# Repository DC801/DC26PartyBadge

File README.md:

# DC801 DC26 Party Badge
Party badge and BLE hardware board

# Hardware
 - **Rigado BMD-300** Bluetooth low energy based on a Nordic nRF52832
   - 16MHz ARM® Cortex™ M4F CPU, 512kB of flash memory, 64kB RAM
   - [https://www.rigado.com/product/bmd-300/](https://www.rigado.com/product/bmd-300/)
 ***
 - **Lots of I/O**
   - Speaker
   - 6 buttons
   - One hidden button
   - SPI LCD screen
   - Selected pin breakouts
   - JTAG interface
   - Micro USB
   - microSD card
   - 2 SAO connectors
   - 2 minibadges
 ***
 - A MCP73831 LiPo battery charger
 - Kickass silkscreen

Board design is in Kicad

See the [Hardware](/Hardware) directory for more info, schematics and etc

# SD Card

Format your SD card as FAT32 and copy the contents of [SD_Card](SD_Card) into it

# Software
 - Environment is GNU ARM GCC with your choice of IDE (I used CLion)
 - Need a J-Link Segger JTAG programmer
 - Uses the softdevice s132

See the [Software](/Software) directory for more info

# What's it do?

Awesome **things**, that's what!  See the [Software](Software) directory for more information.

# More info

Follow [@rushan_ee](http://twitter.com/rushan_ee) or [@hamster](http://twitter.com/hamster) for updates

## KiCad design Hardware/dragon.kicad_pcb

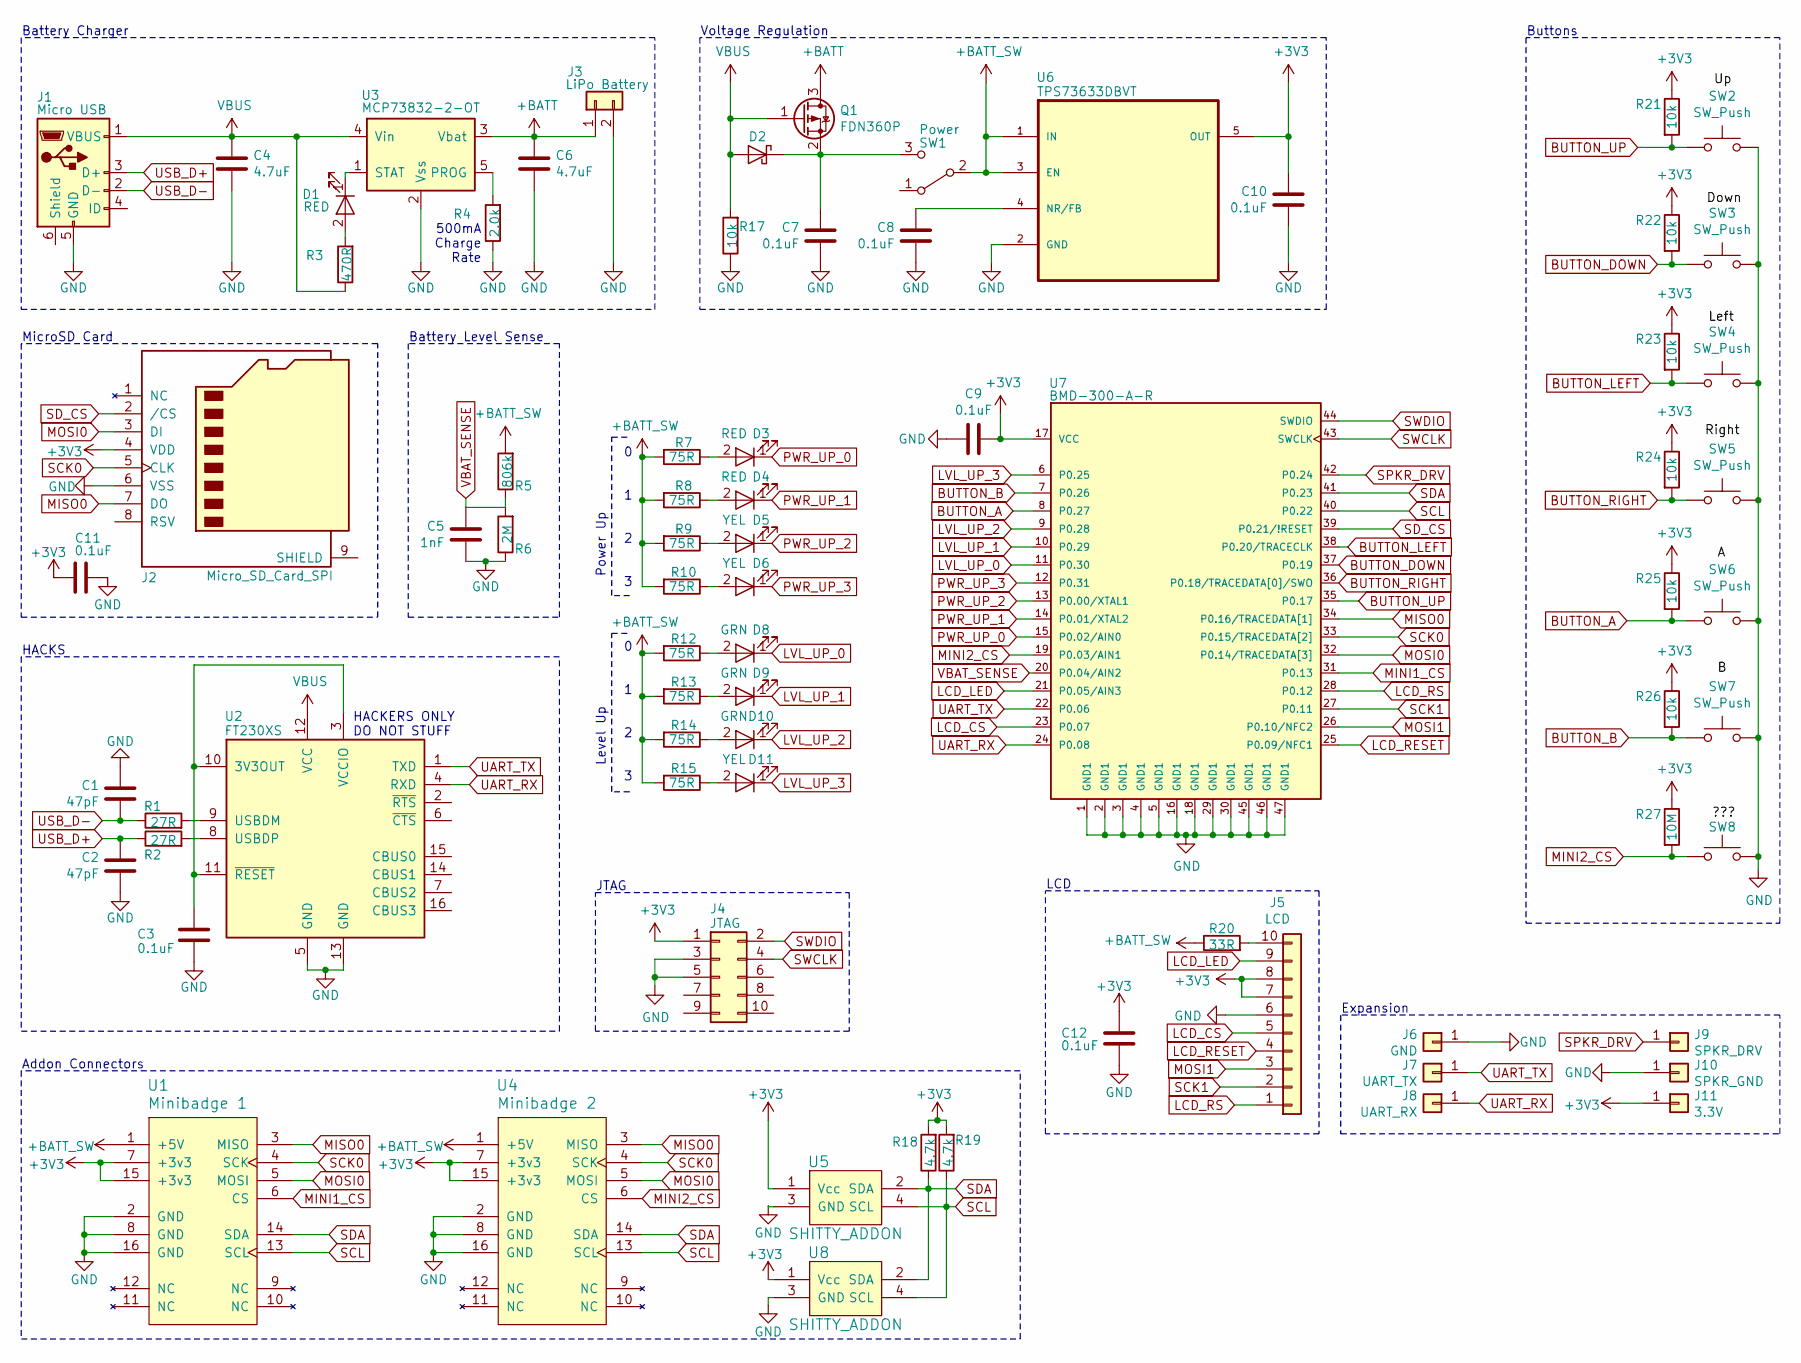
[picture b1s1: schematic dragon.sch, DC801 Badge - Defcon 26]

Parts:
C1, C2: 47pF; C_0201
C3, C7, C8, C9, C10, C11, C12: 0.1uF; C_0201
C4, C6: 4.7uF; C_0603
C5: 1nF; C_0201
D1, D3, D4: RED; LED_0603
D2: D_Schottky; D_0603
D5, D6, D11: YEL; LED_0603
D8, D9, D10: GRN; LED_0603
J1: Micro USB; MicroUSB-10118192-0001LF
J2: Micro_SD_Card_SPI; MicroSD-Socket-1140084168
J3: LiPo Battery; JST_PH_S2B-PH-SM4-TB_02x2.00mm_Angled
J4: JTAG; Pin_Header_Straight_2x05_Pitch1.27mm_SMD
J5: LCD; XF2L-1035-1A
J6: GND; SolderWirePad_single_0-8mmDrill
J7: UART_TX; SolderWirePad_single_0-8mmDrill
J8: UART_RX; SolderWirePad_single_0-8mmDrill
J9: SPKR_DRV; SolderWirePad_single_0-8mmDrill
J10: SPKR_GND; SolderWirePad_single_0-8mmDrill
J11: 3.3V; SolderWirePad_single_0-8mmDrill
Q1: FDN360P; SuperSOT-3
R1, R2: 27R; R_0201
R3: 470R; R_0201
R4: 2.0k; R_0201
R5: 806k; R_0201
R6: 2M; R_0201
R7, R8, R9, R10, R12, R13, R14, R15: 75R; R_0201
R17, R21, R22, R23, R24, R25, R26: 10k; R_0201
R18, R19: 4.7k; R_0201
R20: 33R; R_0201
R27: 10M; R_0201
SW1: Power; SW_SPDT_CK-JS102011SAQN
SW2, SW3, SW4, SW5, SW6, SW7: SW_Push; SW_SPST_B3S-1000
SW8: TEST_2P; Test_Point_2Pads
U1: Minibadge 1; SAINTCON-Minibadge
U2: FT230XS; SSOP-16_3.9x4.9mm_Pitch0.635mm
U3: MCP73832-2-OT; TSOT-23-5
U4: Minibadge 2; SAINTCON-Minibadge
U5, U8: SHITTY_ADDON; Badgelife-Shitty-2x2-NotRotated
U6: TPS73633DBVT; TSOT-23-5
U7: BMD-300-A-R; RIGADO_BMD-300-A-R

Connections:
+3V3: C9.1, C10.1, C11.2, C12.2, J2.4 (VDD), J4.1, J5.7, J5.8, J11.1, R18.2, R19.2, R21.1, R22.1, R23.1, R24.1, R25.1, R26.1, R27.1, U1.7 (+3v3), U1.15 (+3v3), U4.7 (+3v3), U4.15 (+3v3), U5.1 (Vcc), U6.5 (OUT), U7.17 (VCC), U8.1 (Vcc)
+BATT: C6.2, J3.1, Q1.3 (D), U3.3 (Vbat)
+BATT_SW: R5.2, R7.2, R8.2, R9.2, R10.2, R12.2, R13.2, R14.2, R15.2, R20.1, SW1.2 (B), U1.1 (+5V), U4.1 (+5V), U6.1 (IN), U6.3 (EN)
BUTTON_A: R25.2, SW6.1, U7.8 (P0.27)
BUTTON_B: R26.2, SW7.1, U7.7 (P0.26)
BUTTON_DOWN: R22.2, SW3.1, U7.37 (P0.19)
BUTTON_LEFT: R23.2, SW4.1, U7.38 (P0.20/TRACECLK)
BUTTON_RIGHT: R24.2, SW5.1, U7.36 (P0.18/TRACEDATA[0]/SWO)
BUTTON_UP: R21.2, SW2.1, U7.35 (P0.17)
GND: C1.1, C2.2, C3.1, C4.1, C5.2, C6.1, C7.2, C8.2, C9.2, C10.2, C11.1, C12.1, J1.5 (GND), J2.6 (VSS), J3.2, J4.3, J4.5, J5.6, J6.1, J10.1, R4.1, R6.1, R17.1, SW2.2, SW3.2, SW4.2, SW5.2, SW6.2, SW7.2, SW8.2, U1.2 (GND), U1.8 (GND), U1.16 (GND), U2.5 (GND), U2.13 (GND), U3.2 (Vss), U4.2 (GND), U4.8 (GND), U4.16 (GND), U5.3 (GND), U6.2 (GND), U7.1 (GND1), U7.2 (GND1), U7.3 (GND1), U7.4 (GND1), U7.5 (GND1), U7.16 (GND1), U7.18 (GND1), U7.29 (GND1), U7.30 (GND1), U7.45 (GND1), U7.46 (GND1), U7.47 (GND1), U8.3 (GND)
LCD_CS: J5.5, U7.23 (P0.07)
LCD_LED: J5.9, U7.21 (P0.05/AIN3)
LCD_RESET: J5.4, U7.25 (P0.09/NFC1)
LCD_RS: J5.1, U7.28 (P0.12)
LVL_UP_0: D8.1 (K), U7.11 (P0.30)
LVL_UP_1: D9.1 (K), U7.10 (P0.29)
LVL_UP_2: D10.1 (K), U7.9 (P0.28)
LVL_UP_3: D11.1 (K), U7.6 (P0.25)
MINI1_CS: U1.6 (CS), U7.31 (P0.13)
MINI2_CS: R27.2, SW8.1, U4.6 (CS), U7.19 (P0.03/AIN1)
MISO0: J2.7 (DO), U1.3 (MISO), U4.3 (MISO), U7.34 (P0.16/TRACEDATA[1])
MOSI0: J2.3 (DI), U1.5 (MOSI), U4.5 (MOSI), U7.32 (P0.14/TRACEDATA[3])
MOSI1: J5.3, U7.26 (P0.10/NFC2)
unnamed: C3.2, U2.3 (VCCIO), U2.10 (3V3OUT), U2.11 (~RESET)
unnamed: C7.1, D2.1 (K), Q1.2 (S), SW1.3 (C)
unnamed: C8.1, U6.4 (NR/FB)
unnamed: D1.1 (K), U3.1 (STAT)
unnamed: D1.2 (A), R3.2
unnamed: D3.2 (A), R7.1
unnamed: D4.2 (A), R8.1
unnamed: D5.2 (A), R9.1
unnamed: D6.2 (A), R10.1
unnamed: D8.2 (A), R12.1
unnamed: D9.2 (A), R13.1
unnamed: D10.2 (A), R14.1
unnamed: D11.2 (A), R15.1
unnamed: J5.10, R20.2
unnamed: R1.2, U2.9 (USBDM)
unnamed: R2.2, U2.8 (USBDP)
unnamed: R4.2, U3.5 (PROG)
PWR_UP_0: D3.1 (K), U7.15 (P0.02/AIN0)
PWR_UP_1: D4.1 (K), U7.14 (P0.01/XTAL2)
PWR_UP_2: D5.1 (K), U7.13 (P0.00/XTAL1)
PWR_UP_3: D6.1 (K), U7.12 (P0.31)
SCK0: J2.5 (CLK), U1.4 (SCK), U4.4 (SCK), U7.33 (P0.15/TRACEDATA[2])
SCK1: J5.2, U7.27 (P0.11)
SCL: R19.1, U1.13 (SCL), U4.13 (SCL), U5.4 (SCL), U7.40 (P0.22), U8.4 (SCL)
SDA: R18.1, U1.14 (SDA), U4.14 (SDA), U5.2 (SDA), U7.41 (P0.23), U8.2 (SDA)
SD_CS: J2.2 (/CS), U7.39 (P0.21/!RESET)
SPKR_DRV: J9.1, U7.42 (P0.24)
SWCLK: J4.4, U7.43 (SWCLK)
SWDIO: J4.2, U7.44 (SWDIO)
UART_RX: J8.1, U2.4 (RXD), U7.24 (P0.08)
UART_TX: J7.1, U2.1 (TXD), U7.22 (P0.06)
USB_D+: C2.1, J1.3 (D+), R2.1
USB_D-: C1.2, J1.2 (D-), R1.1
VBAT_SENSE: C5.1, R5.1, R6.2, U7.20 (P0.04/AIN2)
VBUS: C4.2, D2.2 (A), J1.1 (VBUS), Q1.1 (G), R3.1, R17.2, U2.12 (VCC), U3.4 (Vin)

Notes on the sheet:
Power Up
Level Up
500mA Charge Rate
Buttons
LCD
Voltage Regulation
Battery Charger
MicroSD Card
Battery Level Sense
HACKS
HACKERS ONLY DO NOT STUFF
Addon Connectors
Expansion
JTAG

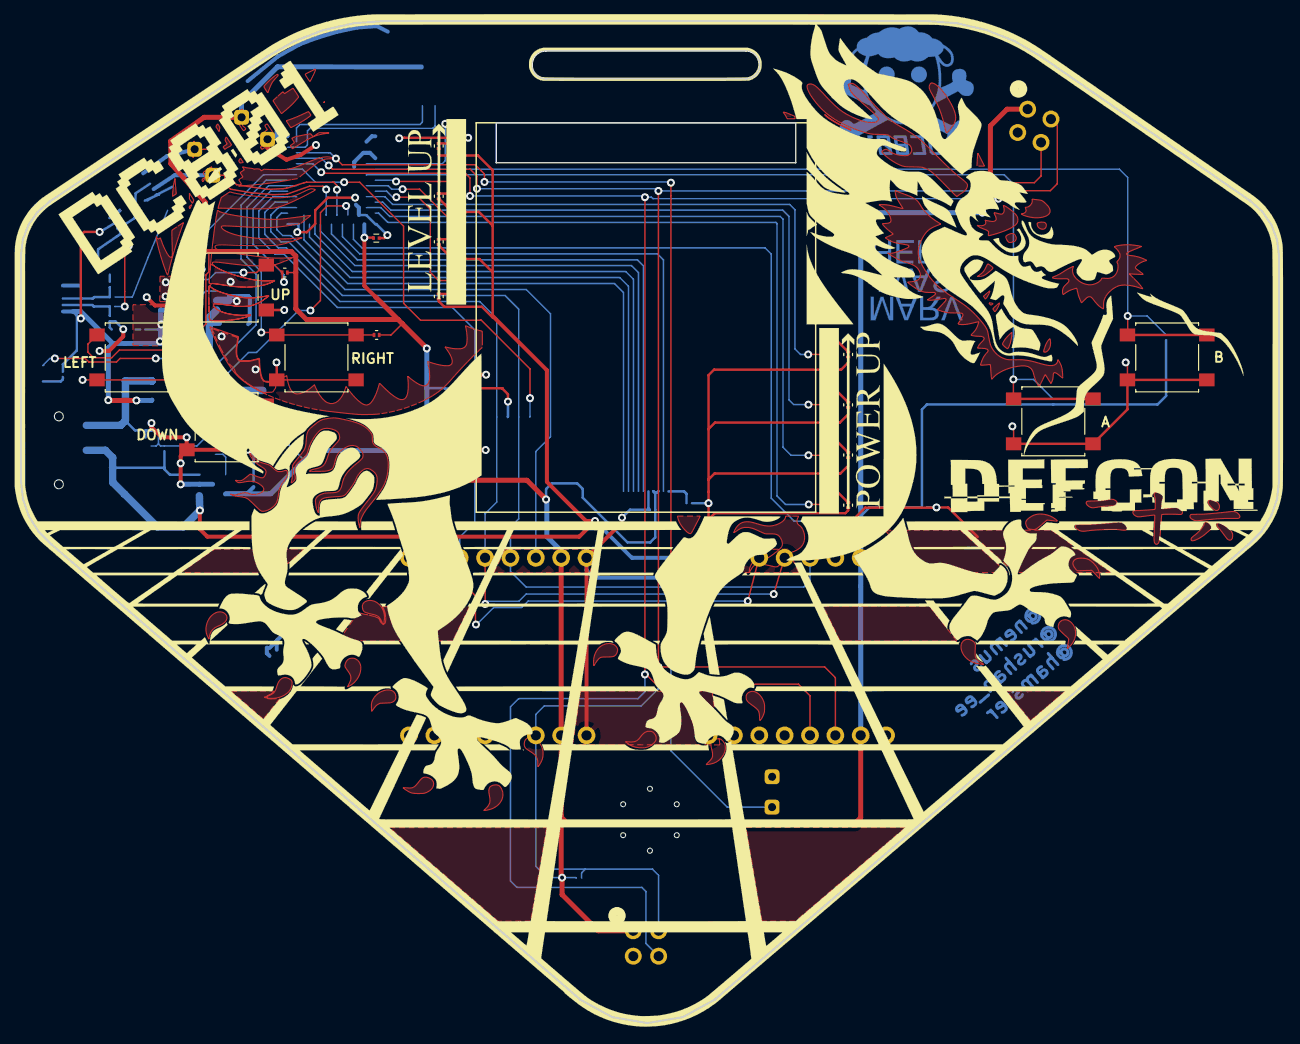
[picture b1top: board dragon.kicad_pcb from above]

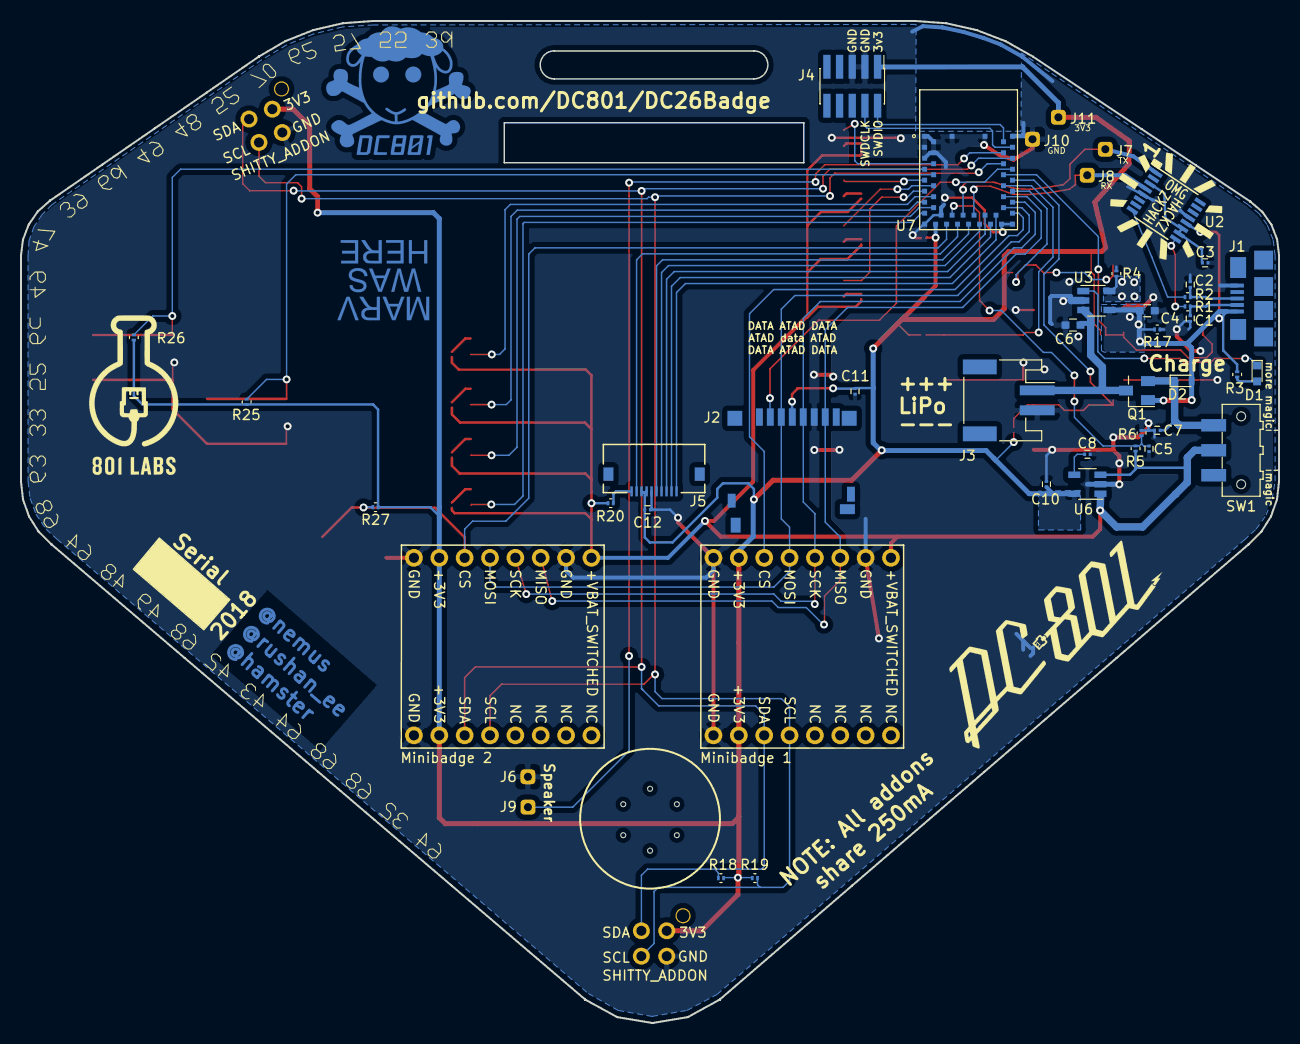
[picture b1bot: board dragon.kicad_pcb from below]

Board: 2 copper layers, 126.0 x 100.4 mm, 74 parts (43 on the bottom side), 58 nets.

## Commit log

2018-08-18 Publishing the design files for the DC801 DC26 badge
2019-07-24 add DC27 badges
2019-07-24 remove stupid comments
2019-08-29 Adding pdf export of the schematic

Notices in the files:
parts and their libraries:
Copyright 2016 Accelerated Designs. All rights reserved.
